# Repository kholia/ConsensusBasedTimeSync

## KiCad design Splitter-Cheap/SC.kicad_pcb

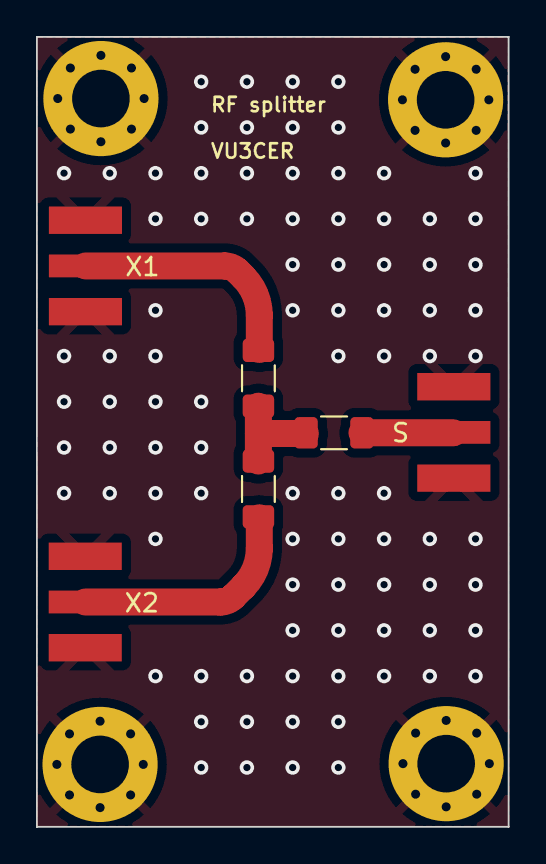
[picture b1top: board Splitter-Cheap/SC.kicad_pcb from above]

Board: 2 copper layers, 26.2 x 43.9 mm, 10 parts (0 on the bottom side), 5 nets.

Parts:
H1, H2, H3, H4: MountingHole_Pad; MountingHole_3.2mm_M3_Pad_Via
R1, R2, R3: 16.7R; R_1206_3216Metric_Pad1.30x1.75mm_HandSolder
SMA1: X1; SMA_EDGELAUNCH_Modded
SMA2: X2; SMA_EDGELAUNCH_Modded
SMA3: S; SMA_EDGELAUNCH_Modded

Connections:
GND: H1.1, H2.1, H3.1, H4.1, SMA1.2 (Ext), SMA2.2 (Ext), SMA3.2 (Ext)
unnamed: R1.1, R2.2, R3.1
unnamed: R1.2, SMA1.1 (In)
unnamed: R3.2, SMA2.1 (In)
unnamed: R2.1, SMA3.1 (In)

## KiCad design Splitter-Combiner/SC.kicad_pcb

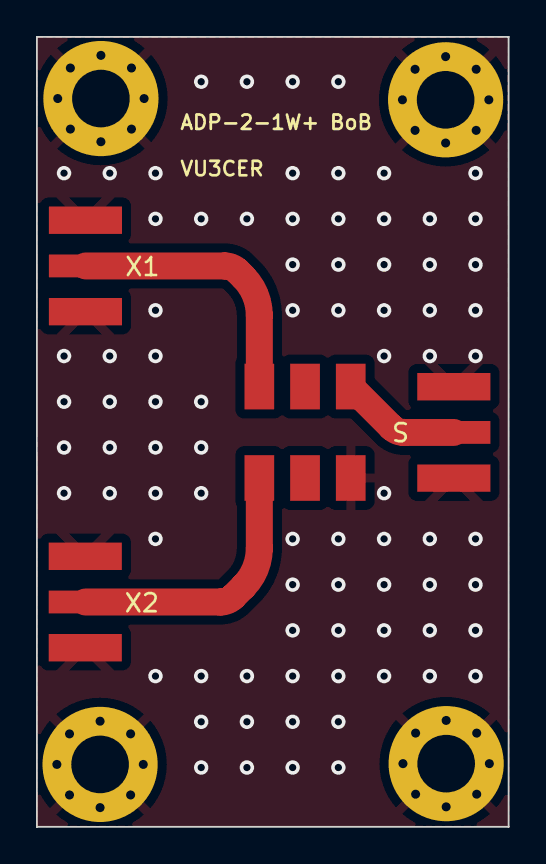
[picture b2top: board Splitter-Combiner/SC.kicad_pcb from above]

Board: 2 copper layers, 26.2 x 43.9 mm, 8 parts (0 on the bottom side), 4 nets.

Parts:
H1, H2, H3, H4: MountingHole_Pad; MountingHole_3.2mm_M3_Pad_Via
SMA1: X1; SMA_EDGELAUNCH_Modded
SMA2: X2; SMA_EDGELAUNCH_Modded
SMA3: S; SMA_EDGELAUNCH_Modded
U1: ADP-2-1W+; MC-CDXXX-Modded

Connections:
GND: H1.1, H2.1, H3.1, H4.1, SMA1.2 (Ext), SMA2.2 (Ext), SMA3.2 (Ext), U1.6
unnamed: SMA1.1 (In), U1.3
unnamed: SMA2.1 (In), U1.4
unnamed: SMA3.1 (In), U1.1
